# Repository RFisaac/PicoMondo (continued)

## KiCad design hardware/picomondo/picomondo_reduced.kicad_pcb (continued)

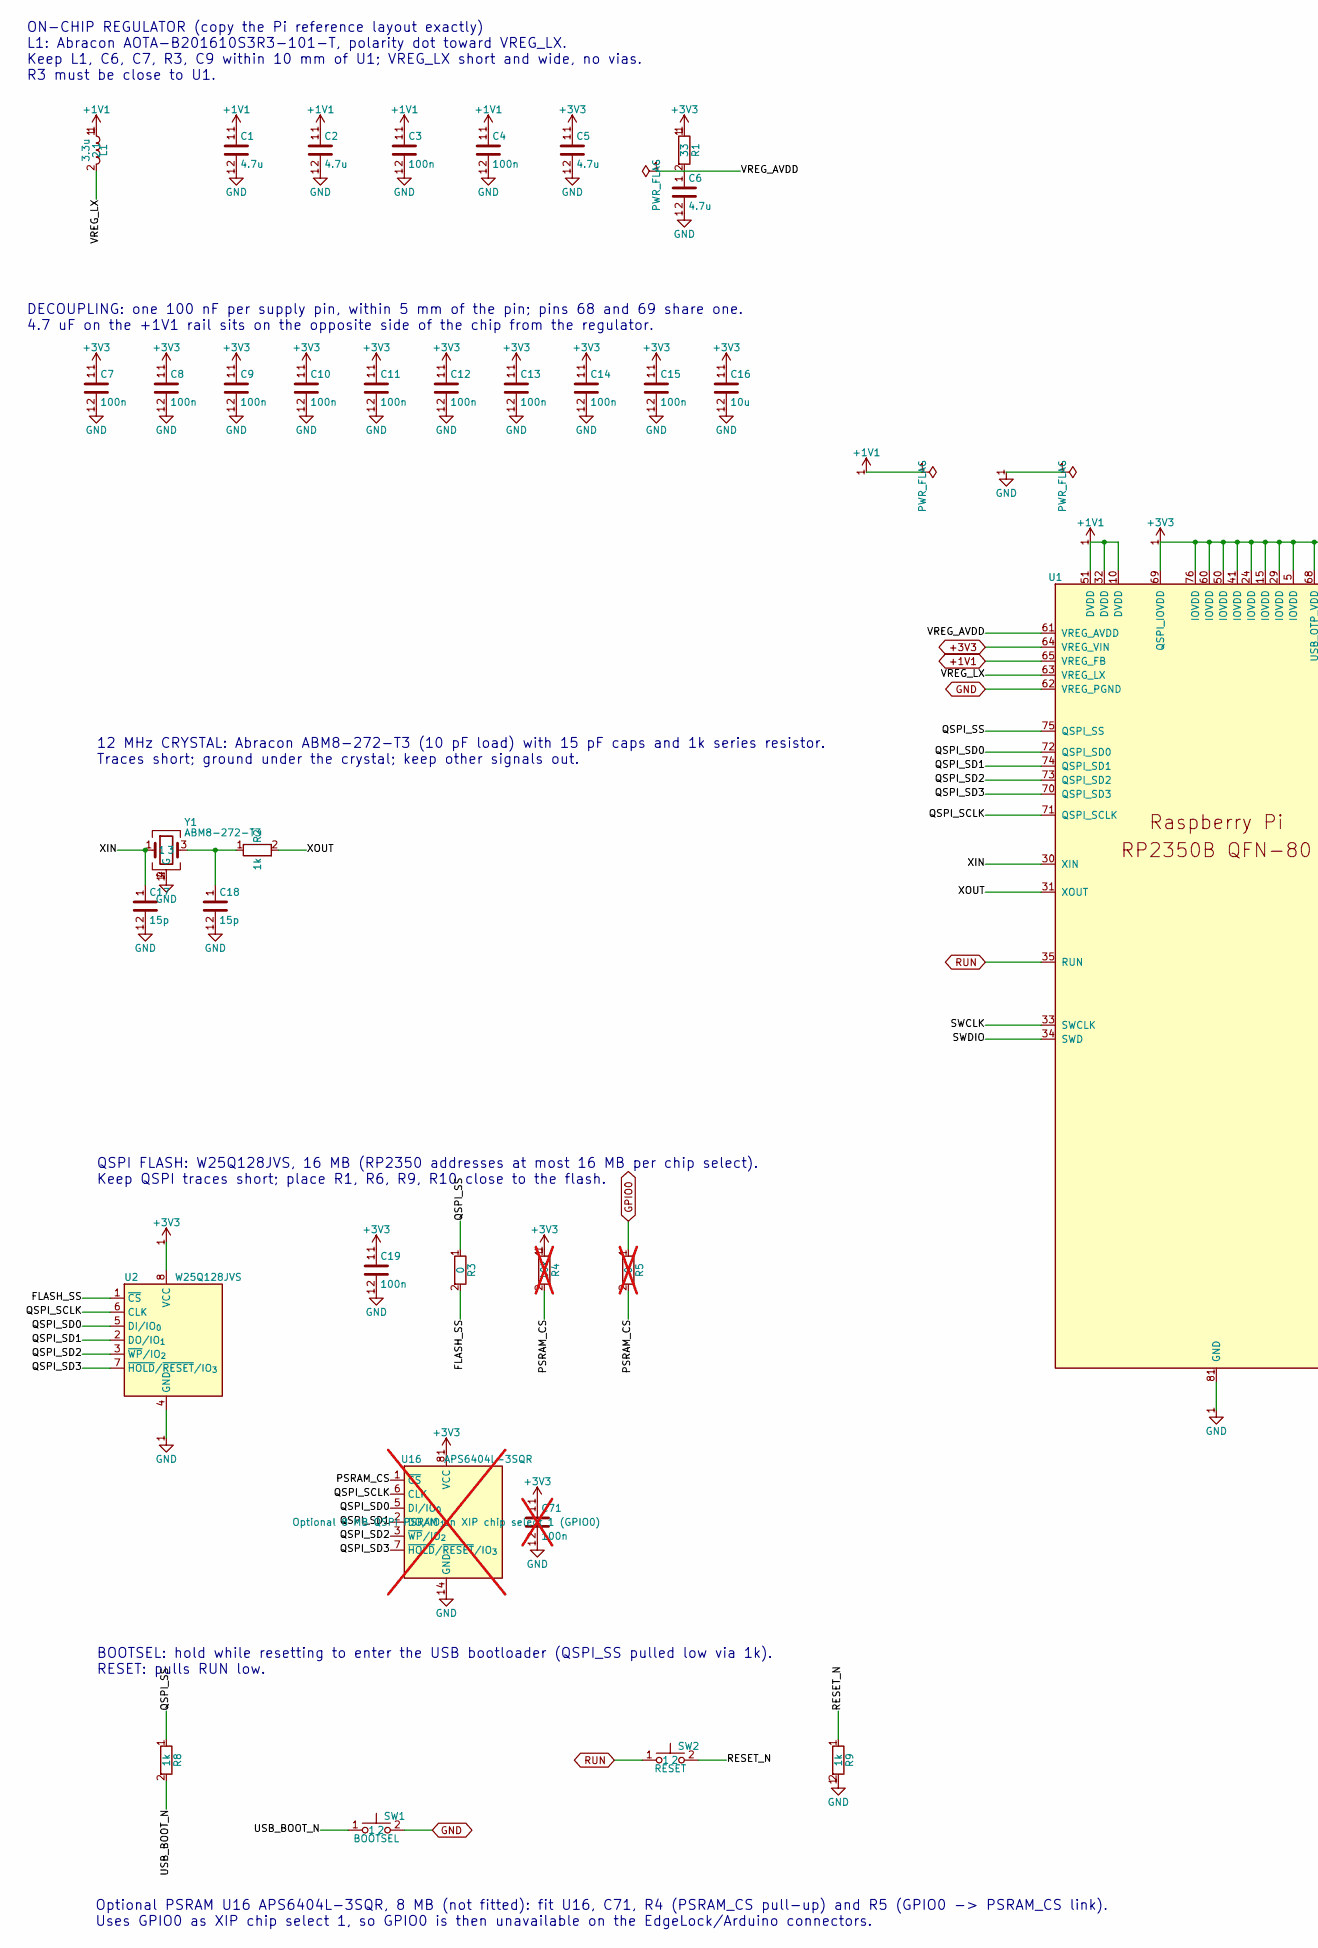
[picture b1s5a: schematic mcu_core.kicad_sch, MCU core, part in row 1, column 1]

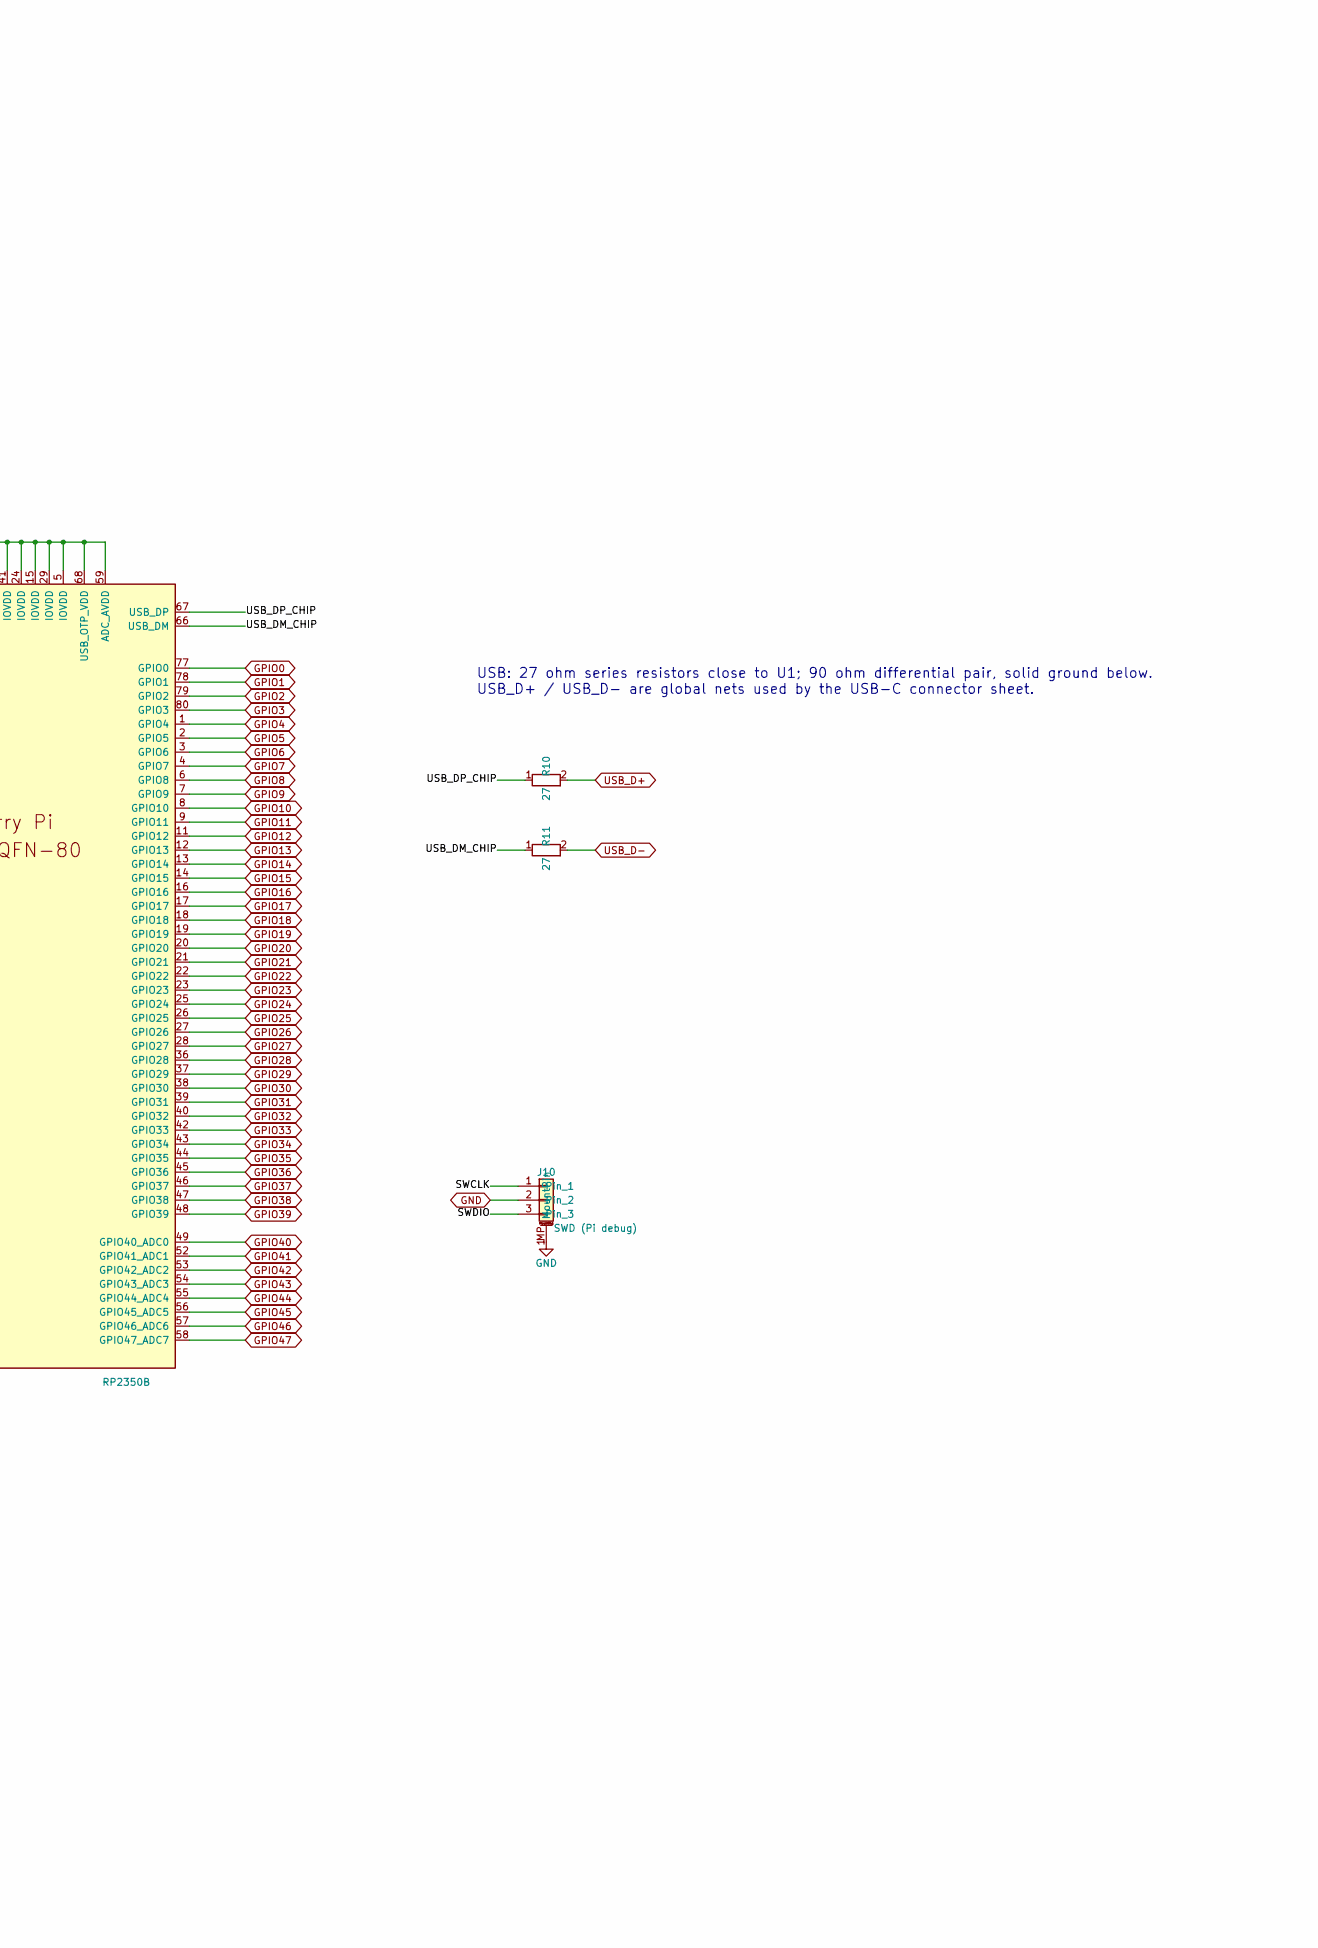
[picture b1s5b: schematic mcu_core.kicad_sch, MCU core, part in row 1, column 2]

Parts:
C1, C2, C5, C6: 4.7u; C_0402_1005Metric_small_pads; MPN CL05A475MP5NRNC; LCSC C23733
C3, C4, C7, C8, C9, C10, C11, C12, C13, C14, C15, C19: 100n; C_0402_1005Metric; MPN CL05B104KB54PNC; LCSC C307331
C16: 10u; C_0805_2012Metric; MPN CL21A106KAYNNNE; LCSC C15850
C17, C18: 15p; C_0402_1005Metric; MPN CC0402JRNPO9BN150; LCSC C106997
C71: 100n; C_0402_1005Metric; MPN CL05B104KB54PNC; LCSC C307331; not fitted
J10: SWD (Pi debug); JST_SH_SM03B-SRSS-TB_1x03-1MP_P1.00mm_Horizontal; MPN SM03B-SRSS-TB(LF)(SN); LCSC C160403
L1: 3.3u; L_pol_2016; MPN AOTA-B201610S3R3-101-T; LCSC C42411119
R1: 33; R_0402_1005Metric; MPN 0402WGF330JTCE; LCSC C25105
R2, R8, R9: 1k; R_0402_1005Metric; MPN 0402WGF1001TCE; LCSC C11702
R3: 0; R_0402_1005Metric; MPN 0402WGF0000TCE; LCSC C17168
R4: 10k; R_0402_1005Metric; MPN 0402WGF1002TCE; LCSC C25744; not fitted
R5: 0; R_0402_1005Metric; MPN 0402WGF0000TCE; LCSC C17168; not fitted
R10, R11: 27; R_0402_1005Metric; MPN 0402WGF270JTCE; LCSC C25100
SW1: BOOTSEL; SW_SMD_TS-1187A_5.1x5.1; MPN TS-1187A-B-A-B; LCSC C318884
SW2: RESET; SW_SMD_TS-1187A_5.1x5.1; MPN TS-1187A-B-A-B; LCSC C318884
U1: RP2350B; RP2350-QFN-80-1EP_10x10_P0.4mm_EP3.4x3.4mm_ThermalVias; MPN RP2350B; LCSC C42415655
U2: W25Q128JVS; SOIC-8_5.3x5.3mm_P1.27mm; MPN W25Q128JVSIQ; LCSC C97521
U16: APS6404L-3SQR; SOIC-8_3.9x4.9mm_P1.27mm; MPN APS6404L-3SQR-SN; LCSC C5333729; not fitted
Y1: ABM8-272-T3; Crystal_SMD_3225-4Pin_3.2x2.5mm; MPN ABM8-272-T3; LCSC C20625731

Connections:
+1V1: C1.1, C2.1, C3.1, C4.1, L1.1, U1.10 (DVDD), U1.32 (DVDD), U1.51 (DVDD), U1.65 (VREG_FB); also elsewhere on the board
+3V3: C5.1, C7.1, C8.1, C9.1, C10.1, C11.1, C12.1, C13.1, C14.1, C15.1, C16.1, C19.1, C71.1, R1.1, R4.1, U1.5 (IOVDD), U1.15 (IOVDD), U1.24 (IOVDD), U1.29 (IOVDD), U1.41 (IOVDD), U1.50 (IOVDD), U1.59 (ADC_AVDD), U1.60 (IOVDD), U1.64 (VREG_VIN), U1.68 (USB_OTP_VDD), U1.69 (QSPI_IOVDD), U1.76 (IOVDD), U2.8 (VCC), U16.8 (VCC); also elsewhere on the board
/MCU core/FLASH_SS: R3.2, U2.1 (~CS)
/MCU core/PSRAM_CS: R4.2, R5.2, U16.1 (~CS)
/MCU core/QSPI_SCLK: U1.71 (QSPI_SCLK), U2.6 (CLK), U16.6 (CLK)
/MCU core/QSPI_SD0: U1.72 (QSPI_SD0), U2.5 (DI/IO_{0}), U16.5 (DI/IO_{0})
/MCU core/QSPI_SD1: U1.74 (QSPI_SD1), U2.2 (DO/IO_{1}), U16.2 (DO/IO_{1})
/MCU core/QSPI_SD2: U1.73 (QSPI_SD2), U2.3 (~WP/IO_{2}), U16.3 (~WP/IO_{2})
/MCU core/QSPI_SD3: U1.70 (QSPI_SD3), U2.7 (~HOLD/~RESET/IO_{3}), U16.7 (~HOLD/~RESET/IO_{3})
/MCU core/QSPI_SS: R3.1, R8.1, U1.75 (QSPI_SS)
/MCU core/RESET_N: R9.1, SW2.2
/MCU core/SWCLK: J10.1, U1.33 (SWCLK)
/MCU core/SWDIO: J10.3, U1.34 (SWD)
/MCU core/USB_BOOT_N: R8.2, SW1.1
/MCU core/USB_DM_CHIP: R11.1, U1.66 (USB_DM)
/MCU core/USB_DP_CHIP: R10.1, U1.67 (USB_DP)
/MCU core/VREG_AVDD: C6.1, R1.2, U1.61 (VREG_AVDD)
/MCU core/VREG_LX: L1.2, U1.63 (VREG_LX)
/MCU core/XIN: C17.1, U1.30 (XIN), Y1.1
/MCU core/XOUT: R2.2, U1.31 (XOUT)
GND: C1.2, C2.2, C3.2, C4.2, C5.2, C6.2, C7.2, C8.2, C9.2, C10.2, C11.2, C12.2, C13.2, C14.2, C15.2, C16.2, C17.2, C18.2, C19.2, C71.2, J10.2, J10.MP (MountPin), R9.2, SW1.2, U1.62 (VREG_PGND), U1.81 (GND), U2.4 (GND), U16.4 (GND), Y1.2 (G), Y1.4 (G); also elsewhere on the board
GPIO0: R5.1, U1.77 (GPIO0); also elsewhere on the board
GPIO1: U1.78 (GPIO1); also elsewhere on the board
GPIO2: U1.79 (GPIO2); also elsewhere on the board
GPIO3: U1.80 (GPIO3); also elsewhere on the board
GPIO4: U1.1 (GPIO4); also elsewhere on the board
GPIO5: U1.2 (GPIO5); also elsewhere on the board
GPIO6: U1.3 (GPIO6); also elsewhere on the board
GPIO7: U1.4 (GPIO7); also elsewhere on the board
GPIO8: U1.6 (GPIO8); also elsewhere on the board
GPIO9: U1.7 (GPIO9); also elsewhere on the board
GPIO10: U1.8 (GPIO10); also elsewhere on the board
GPIO11: U1.9 (GPIO11); also elsewhere on the board
GPIO12: U1.11 (GPIO12); also elsewhere on the board
GPIO13: U1.12 (GPIO13); also elsewhere on the board
GPIO14: U1.13 (GPIO14); also elsewhere on the board
GPIO15: U1.14 (GPIO15); also elsewhere on the board
GPIO16: U1.16 (GPIO16); also elsewhere on the board
GPIO17: U1.17 (GPIO17); also elsewhere on the board
GPIO18: U1.18 (GPIO18); also elsewhere on the board
GPIO19: U1.19 (GPIO19); also elsewhere on the board
GPIO20: U1.20 (GPIO20); also elsewhere on the board
GPIO21: U1.21 (GPIO21); also elsewhere on the board
GPIO22: U1.22 (GPIO22); also elsewhere on the board
GPIO23: U1.23 (GPIO23); also elsewhere on the board
GPIO24: U1.25 (GPIO24); also elsewhere on the board
GPIO25: U1.26 (GPIO25); also elsewhere on the board
GPIO26: U1.27 (GPIO26); also elsewhere on the board
GPIO27: U1.28 (GPIO27); also elsewhere on the board
GPIO28: U1.36 (GPIO28); also elsewhere on the board
GPIO29: U1.37 (GPIO29); also elsewhere on the board
GPIO30: U1.38 (GPIO30); also elsewhere on the board
GPIO31: U1.39 (GPIO31); also elsewhere on the board
GPIO32: U1.40 (GPIO32); also elsewhere on the board
GPIO33: U1.42 (GPIO33); also elsewhere on the board
GPIO34: U1.43 (GPIO34); also elsewhere on the board
GPIO35: U1.44 (GPIO35); also elsewhere on the board
GPIO36: U1.45 (GPIO36); also elsewhere on the board
GPIO37: U1.46 (GPIO37); also elsewhere on the board
GPIO38: U1.47 (GPIO38); also elsewhere on the board
GPIO39: U1.48 (GPIO39); also elsewhere on the board
GPIO40: U1.49 (GPIO40_ADC0); also elsewhere on the board
GPIO41: U1.52 (GPIO41_ADC1); also elsewhere on the board
GPIO42: U1.53 (GPIO42_ADC2); also elsewhere on the board
GPIO43: U1.54 (GPIO43_ADC3); also elsewhere on the board
GPIO44: U1.55 (GPIO44_ADC4); also elsewhere on the board
GPIO45: U1.56 (GPIO45_ADC5); also elsewhere on the board
GPIO46: U1.57 (GPIO46_ADC6); also elsewhere on the board
GPIO47: U1.58 (GPIO47_ADC7); also elsewhere on the board
unnamed: C18.1, R2.1, Y1.3
RUN: SW2.1, U1.35 (RUN)
USB_D+: R10.2; also elsewhere on the board
USB_D-: R11.2; also elsewhere on the board

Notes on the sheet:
BOOTSEL: hold while resetting to enter the USB bootloader (QSPI_SS pulled low via 1k). RESET: pulls RUN low.
12 MHz CRYSTAL: Abracon ABM8-272-T3 (10 pF load) with 15 pF caps and 1k series resistor. Traces short; ground under the crystal; keep other signals out.
ON-CHIP REGULATOR (copy the Pi reference layout exactly) L1: Abracon AOTA-B201610S3R3-101-T, polarity dot toward VREG_LX. Keep L1, C6, C7, R3, C9 within 10 mm of U1; VREG_LX short and wide, no vias. R3 must be close to U1.
Optional PSRAM U16 APS6404L-3SQR, 8 MB (not fitted): fit U16, C71, R4 (PSRAM_CS pull-up) and R5 (GPIO0 -> PSRAM_CS link). Uses GPIO0 as XIP chip select 1, so GPIO0 is then unavailable on the EdgeLock/Arduino connectors.
QSPI FLASH: W25Q128JVS, 16 MB (RP2350 addresses at most 16 MB per chip select). Keep QSPI traces short; place R1, R6, R9, R10 close to the flash.
DECOUPLING: one 100 nF per supply pin, within 5 mm of the pin; pins 68 and 69 share one. 4.7 uF on the +1V1 rail sits on the opposite side of the chip from the regulator.
USB: 27 ohm series resistors close to U1; 90 ohm differential pair, solid ground below. USB_D+ / USB_D- are global nets used by the USB-C connector sheet.

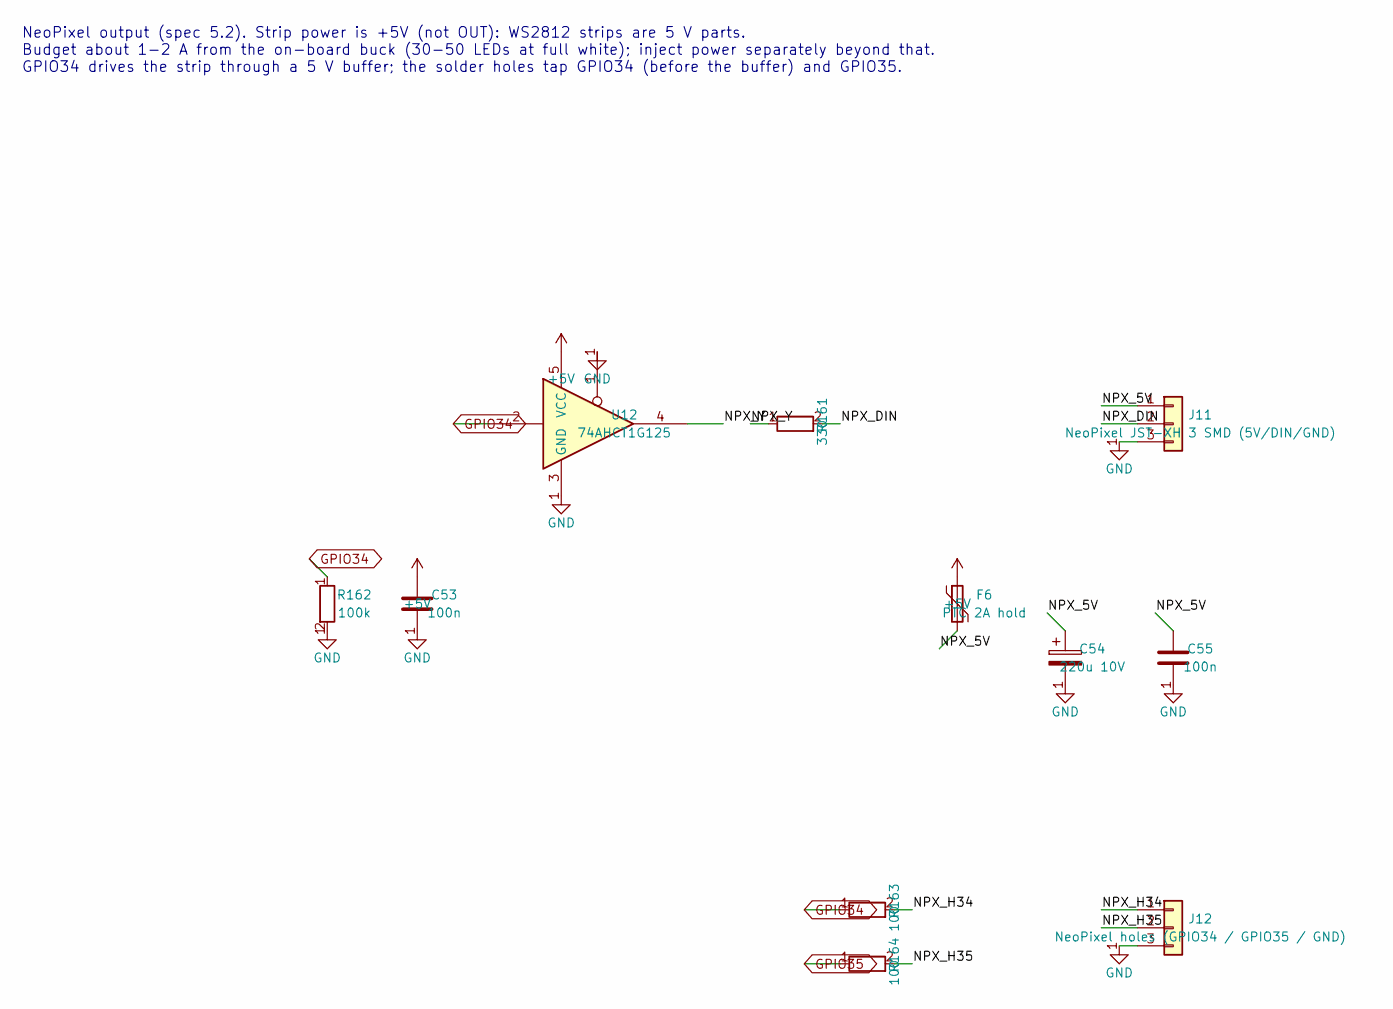
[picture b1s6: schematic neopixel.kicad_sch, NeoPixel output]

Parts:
C53, C55: 100n; C_0402_1005Metric; MPN CL05B104KB54PNC; LCSC C307331
C54: 220u 10V; CP_Elec_6.3x7.7; MPN VMMC0771A221MV; LCSC C487024
F6: PTC 2A hold; F1812; MPN SMD1812P200TF/16; LCSC C20812
J11: NeoPixel JST-XH 3 SMD (5V/DIN/GND); JST_XH_S3B-XH-SM4-TB_1x03-1MP_P2.50mm_Horizontal; MPN S3B-XH-SM4-TB(LF)(SN)
J12: NeoPixel holes (GPIO34 / GPIO35 / GND); PinHeader_1x03_P2.54mm_Vertical
R161: 330; R_0402_1005Metric; MPN 0402WGF3300TCE; LCSC C25104
R162: 100k; R_0402_1005Metric; MPN 0402WGF1003TCE; LCSC C25741
R163, R164: 100; R_0402_1005Metric; MPN 0402WGF1000TCE; LCSC C25076
U12: 74AHCT1G125; SOT-353_SC-70-5; MPN 74AHCT1G125GW,125; LCSC C12495

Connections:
+5V: C53.1, F6.1, U12.5 (VCC); also elsewhere on the board
/NeoPixel and Qwiic/NPX_5V: C54.1, C55.1, F6.2, J11.1
/NeoPixel and Qwiic/NPX_DIN: J11.2, R161.2
/NeoPixel and Qwiic/NPX_H34: J12.1, R163.2
/NeoPixel and Qwiic/NPX_H35: J12.2, R164.2
/NeoPixel and Qwiic/NPX_Y: R161.1, U12.4
GND: C53.2, C54.2, C55.2, J11.3, J12.3, R162.2, U12.1, U12.3 (GND); also elsewhere on the board
GPIO34: R162.1, R163.1, U12.2; also elsewhere on the board
GPIO35: R164.1; also elsewhere on the board

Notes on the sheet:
NeoPixel output (spec 5.2). Strip power is +5V (not OUT): WS2812 strips are 5 V parts. Budget about 1-2 A from the on-board buck (30-50 LEDs at full white); inject power separately beyond that. GPIO34 drives the strip through a 5 V buffer; the solder holes tap GPIO34 (before the buffer) and GPIO35.

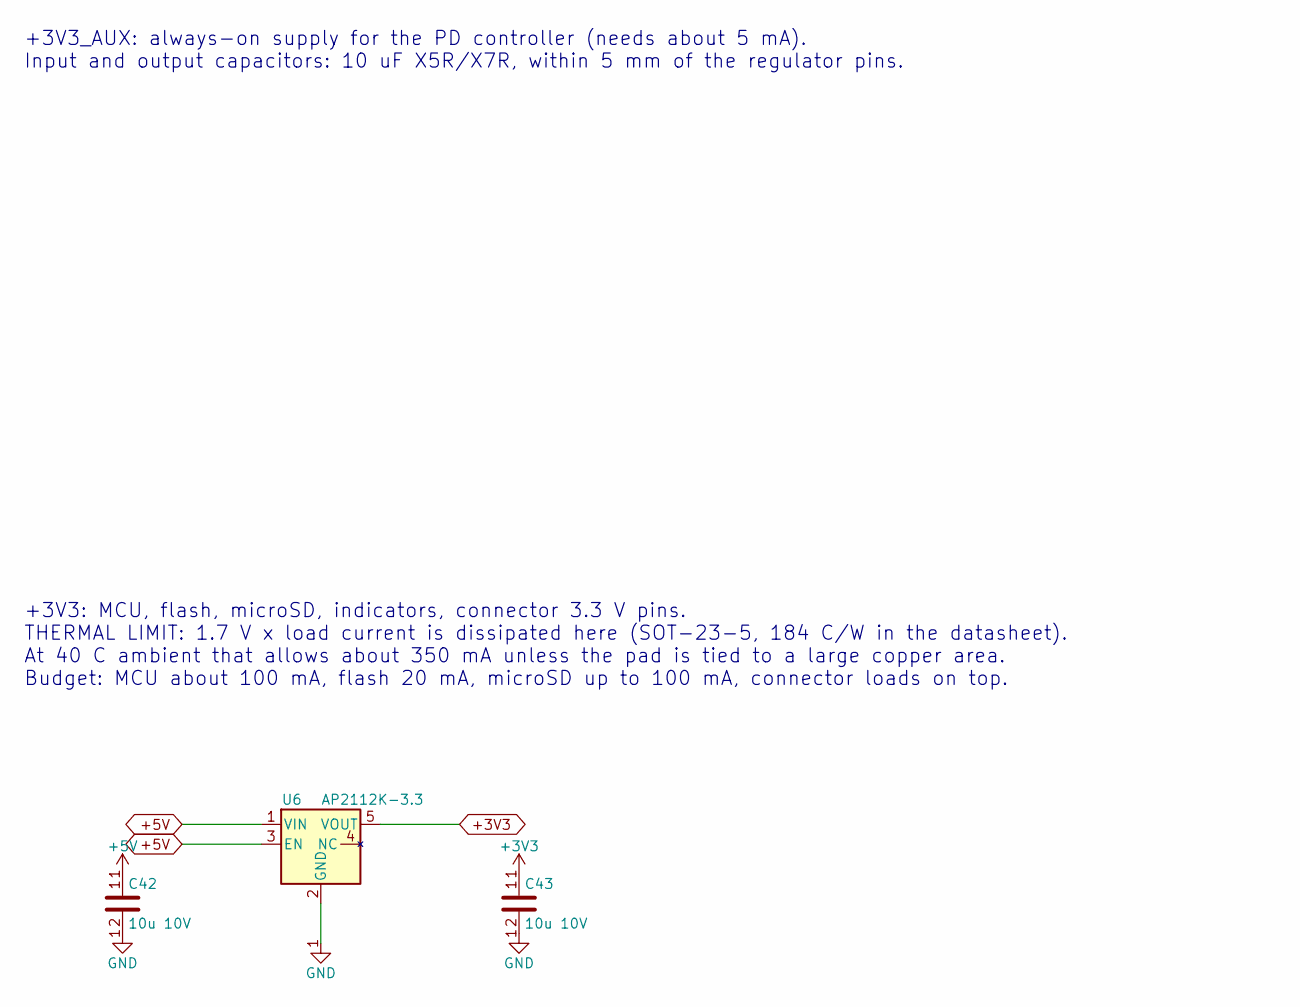
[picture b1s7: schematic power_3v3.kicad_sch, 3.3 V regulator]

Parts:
C42, C43: 10u 10V; C_0805_2012Metric; MPN CL21A106KAYNNNE; LCSC C15850
U6: AP2112K-3.3; SOT-23-5; MPN AP2112K-3.3TRG1; LCSC C51118

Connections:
+3V3: C43.1, U6.5 (VOUT); also elsewhere on the board
+5V: C42.1, U6.1 (VIN), U6.3 (EN); also elsewhere on the board
GND: C42.2, C43.2, U6.2 (GND); also elsewhere on the board

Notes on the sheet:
+3V3_AUX: always-on supply for the PD controller (needs about 5 mA). Input and output capacitors: 10 uF X5R/X7R, within 5 mm of the regulator pins.
+3V3: MCU, flash, microSD, indicators, connector 3.3 V pins. THERMAL LIMIT: 1.7 V x load current is dissipated here (SOT-23-5, 184 C/W in the datasheet). At 40 C ambient that allows about 350 mA unless the pad is tied to a large copper area. Budget: MCU about 100 mA, flash 20 mA, microSD up to 100 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

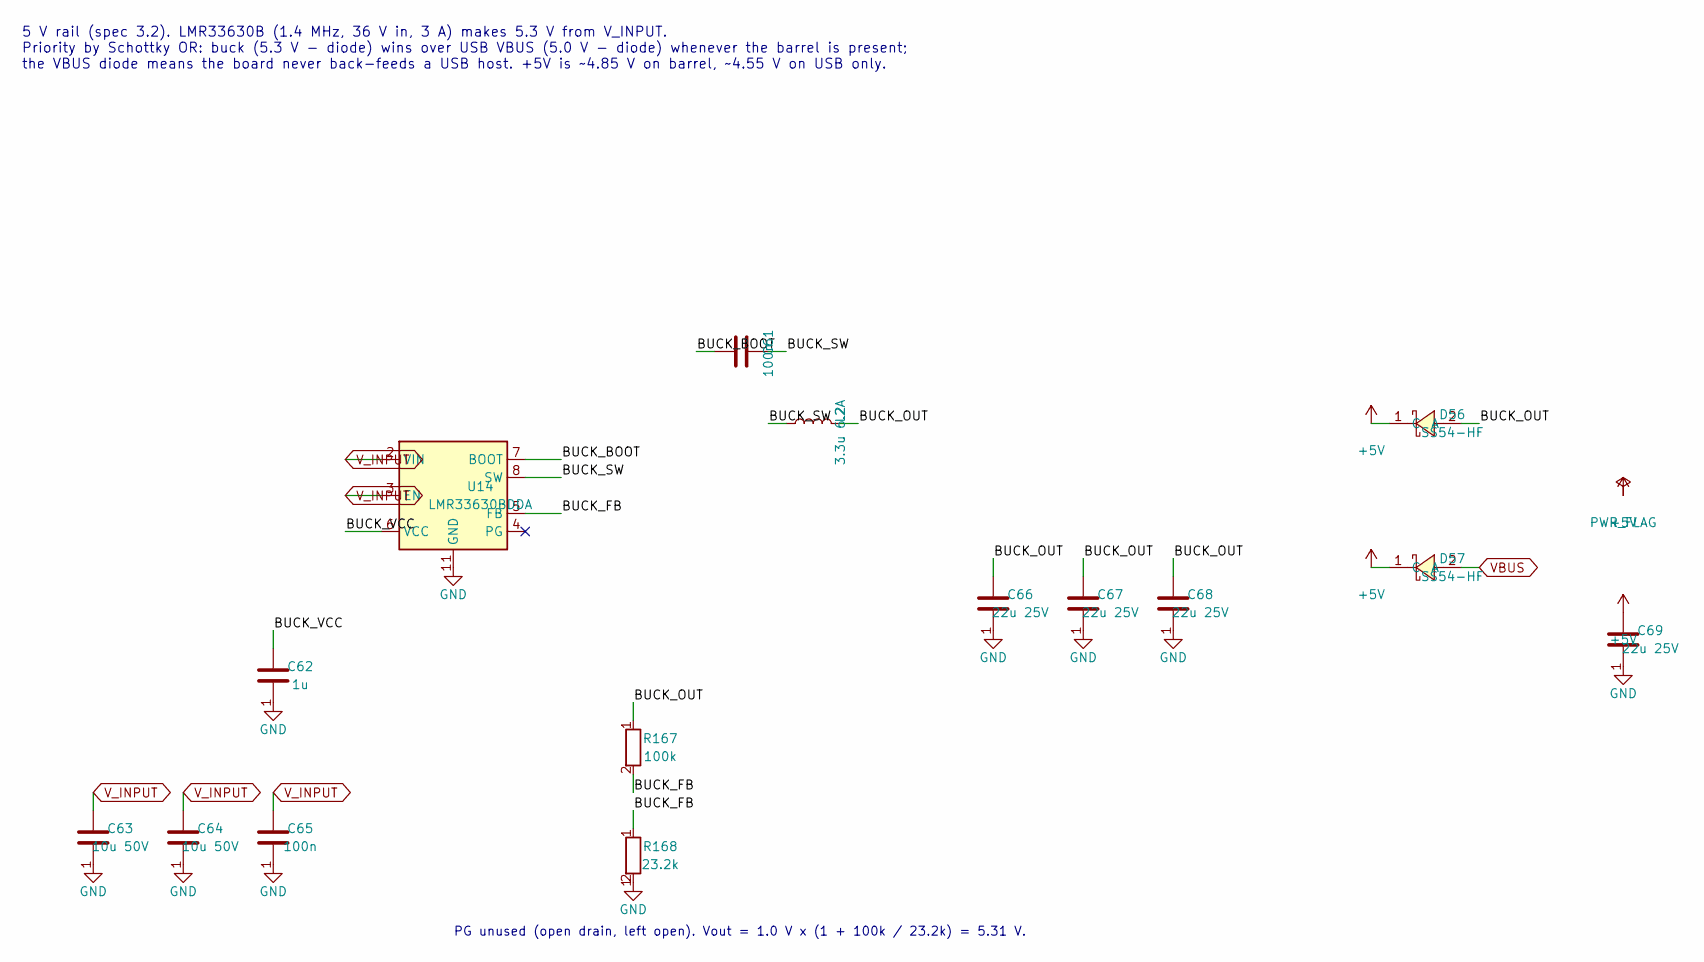
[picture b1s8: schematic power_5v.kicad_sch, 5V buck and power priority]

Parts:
C61, C65: 100n; C_0402_1005Metric; MPN CL05B104KB54PNC; LCSC C307331
C62: 1u; C_0402_1005Metric; MPN CL05A105KA5NQNC; LCSC C52923
C63, C64: 10u 50V; C_1206_3216Metric; MPN CL31A106KBHNNNE; LCSC C13585
C66, C67, C68, C69: 22u 25V; C_1206_3216Metric; MPN CL31A226KAHNNNE; LCSC C12891
D56, D57: SS54-HF; SMA_L4.3-W2.5-LS5.0-RD; MPN SS54-HF; LCSC C3757794
L2: 3.3u 6.2A; L_Sunlord_SWPA6045S; MPN SWPA6045S3R3NT; LCSC C279943
R167: 100k; R_0402_1005Metric; MPN 0402WGF1003TCE; LCSC C25741
R168: 23.2k; R_0402_1005Metric; MPN RC0402FR-0723K2L
U14: LMR33630BDDA; Texas_HSOP-8-1EP_3.9x4.9mm_P1.27mm_ThermalVias; MPN LMR33630BDDAR; LCSC C544370

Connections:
+5V: C69.1, D56.1 (C), D57.1 (C); also elsewhere on the board
/5V and power priority/BUCK_BOOT: C61.1, U14.7 (BOOT)
/5V and power priority/BUCK_FB: R167.2, R168.1, U14.5 (FB)
/5V and power priority/BUCK_OUT: C66.1, C67.1, C68.1, D56.2 (A), L2.2, R167.1
/5V and power priority/BUCK_SW: C61.2, L2.1, U14.8 (SW)
/5V and power priority/BUCK_VCC: C62.1, U14.6 (VCC)
GND: C62.2, C63.2, C64.2, C65.2, C66.2, C67.2, C68.2, C69.2, R168.2, U14.1 (GND), U14.9 (GND); also elsewhere on the board
VBUS: D57.2 (A); also elsewhere on the board
V_INPUT: C63.1, C64.1, C65.1, U14.2 (VIN), U14.3 (EN); also elsewhere on the board

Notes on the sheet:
PG unused (open drain, left open). Vout = 1.0 V x (1 + 100k / 23.2k) = 5.31 V.
5 V rail (spec 3.2). LMR33630B (1.4 MHz, 36 V in, 3 A) makes 5.3 V from V_INPUT. Priority by Schottky OR: buck (5.3 V - diode) wins over USB VBUS (5.0 V - diode) whenever the barrel is present; the VBUS diode means the board never back-feeds a USB host. +5V is ~4.85 V on barrel, ~4.55 V on USB only.

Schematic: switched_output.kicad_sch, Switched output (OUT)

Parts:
C45: 100n; C_0402_1005Metric; MPN CL05B104KB54PNC; LCSC C307331
D6: BZT52C12 12V; D_SOD-123; MPN BZT52C12-13-F; LCSC C177013
D7: SS54-HF; SMA_L4.3-W2.5-LS5.0-RD; MPN SS54-HF; LCSC C3757794
D8: red; LED_0603_1608Metric; MPN KT-0603R; LCSC C2286
F3: 3A hold 33V; F1812; MPN 1812L300/33GR; LCSC C54300298
J8: OUT EdgeLock 4 (2+2); EdgeLock_4ckt_Molex2008900104; MPN 2008900104
J9: OUT heavy holes; EdgeLock_4ckt_HeavyHoles
Q5: DMP4015SSS-13; SO-8_L4.9-W3.9-P1.27-LS5.9-BL; MPN DMP4015SSS-13; LCSC C508210
Q6: MMBT3904; SOT-23; MPN MMBT3904LT1G; LCSC C81464
R27: 20m 1% 2W; R2512; MPN GX2512-2W-20mR-1%; LCSC C500720
R28: 47k; R_0402_1005Metric; MPN 0402WGF4702TCE; LCSC C25792
R29: 22k; R_0603_1608Metric; MPN 0603WAF2202T5E; LCSC C31850
R30, R37: 10k; R_0402_1005Metric; MPN 0402WGF1002TCE; LCSC C25744
R31: 100k; R_0402_1005Metric; MPN 0402WGF1003TCE; LCSC C25741
R32: 22k; R_0402_1005Metric; MPN 0402WGF2202TCE; LCSC C25768
U8: INA226 (0x41); MSOP-10_3x3mm_P0.5mm; MPN INA226AIDGSR; LCSC C49851

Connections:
+3V3: C45.1, U8.2 (A0), U8.6 (VS); also elsewhere on the board
/Switched outputs/J8_BASE: Q6.1 (B), R30.2, R31.1
/Switched outputs/J8_DRAIN: F3.1, Q5.5 (D), Q5.6 (D), Q5.7 (D), Q5.8 (D)
/Switched outputs/J8_GATE: D6.2 (A), Q5.4 (G), R28.2, R29.1
/Switched outputs/J8_GCOL: Q6.3 (C), R29.2
/Switched outputs/J8_OUT: D7.1 (C), F3.2, J8.1, J8.2, J9.1, R32.1, R37.1
/Switched outputs/J8_SRC: D6.1 (K), Q5.1 (S), Q5.2 (S), Q5.3 (S), R27.2, R28.1, U8.8 (Vbus), U8.9 (Vin-)
/Switched outputs/SW_LED: D8.2 (A), R37.2
GND: C45.2, D7.2 (A), D8.1 (K), J8.3, J8.4, J9.2, Q6.2 (E), R31.2, R32.2, U8.1 (A1), U8.7 (GND); also elsewhere on the board
GPIO16: U8.4 (SDA); also elsewhere on the board
GPIO17: U8.5 (SCL); also elsewhere on the board
GPIO24: R30.1; also elsewhere on the board
V_INPUT: R27.1, U8.10 (Vin+); also elsewhere on the board

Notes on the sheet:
+5V_SW: switched 5 V for the J9 servo/motor connector, up to 3 A. GPIO24 high = on. No current monitor. The red LED shows the rail is on.
J7: switched 5 V output, up to 3 A. GPIO8 high = on. INA226 at I2C 0x40. Shunt 20 mohm: the INA226 input range is only +/-81.92 mV, so 3 A needs 27 mohm or less.
J8: switched V_INPUT output (about 5 V to 28 V), up to 3 A. GPIO9 high = on. INA226 at 0x41. 40 V P-FET with a 12 V zener limiting the gate-source voltage; INA226 is rated 36 V.

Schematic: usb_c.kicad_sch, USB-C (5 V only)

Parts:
C70: 4.7u; C_0805_2012Metric; MPN CL21A475KAQNNNE; LCSC C1779
J14: USB-C (USB4105-GF-A); TYPE-C-SMD_SBC-160S1A-20-S412; MPN USB4105-GF-A; LCSC C3020560
R170, R171: 5.1k; R_0402_1005Metric; MPN 0402WGF5101TCE; LCSC C25905
U15: USBLC6-2SC6; SOT-23-6_L2.9-W1.6-P0.95-LS2.8-BL; MPN USBLC6-2SC6; LCSC C7519

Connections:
/USB-C/CC1: J14.A5 (CC1), R170.1
/USB-C/CC2: J14.B5 (CC2), R171.1
GND: C70.2, J14.1 (EH), J14.2 (EH), J14.3 (EH), J14.4 (EH), J14.A1 (GND), J14.A12 (GND), J14.B1 (GND), J14.B12 (GND), R170.2, R171.2, U15.2; also elsewhere on the board
USB_D+: J14.A6 (DP1), J14.B6 (DP2), U15.1, U15.6; also elsewhere on the board
USB_D-: J14.A7 (DN1), J14.B7 (DN2), U15.3, U15.4; also elsewhere on the board
VBUS: C70.1, J14.A4 (VBUS), J14.A9 (VBUS), J14.B4 (VBUS), J14.B9 (VBUS), U15.5; also elsewhere on the board

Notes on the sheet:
USB-C, 5 V only (spec 2): 5.1k on CC1/CC2 (sink), USBLC6-2SC6 at the connector. D+/D- go straight to USB_D+/USB_D- (the 27R series resistors are on the MCU sheet). VBUS goes to the priority diode.

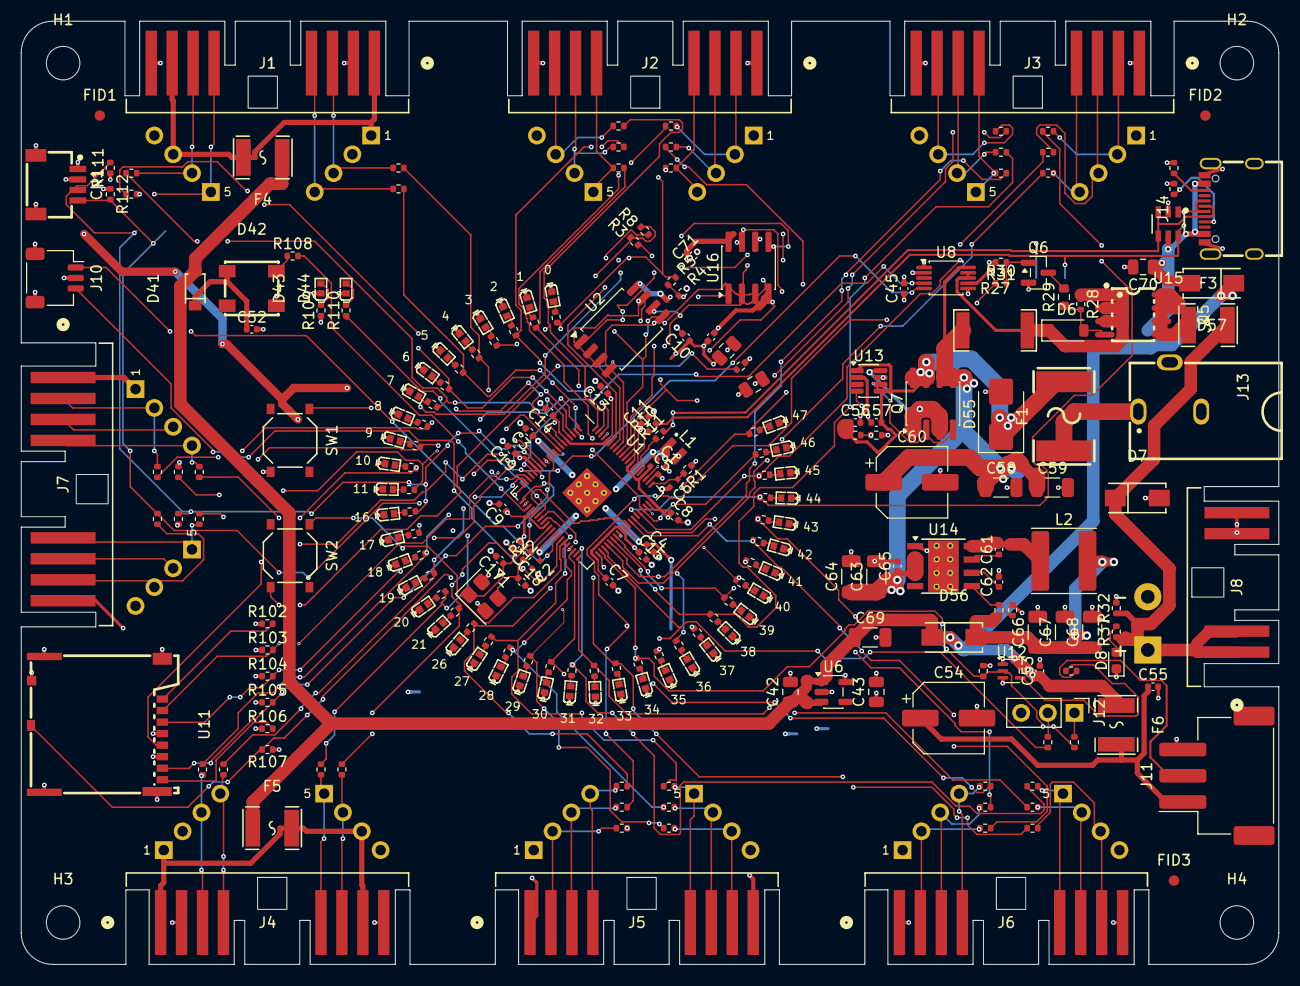
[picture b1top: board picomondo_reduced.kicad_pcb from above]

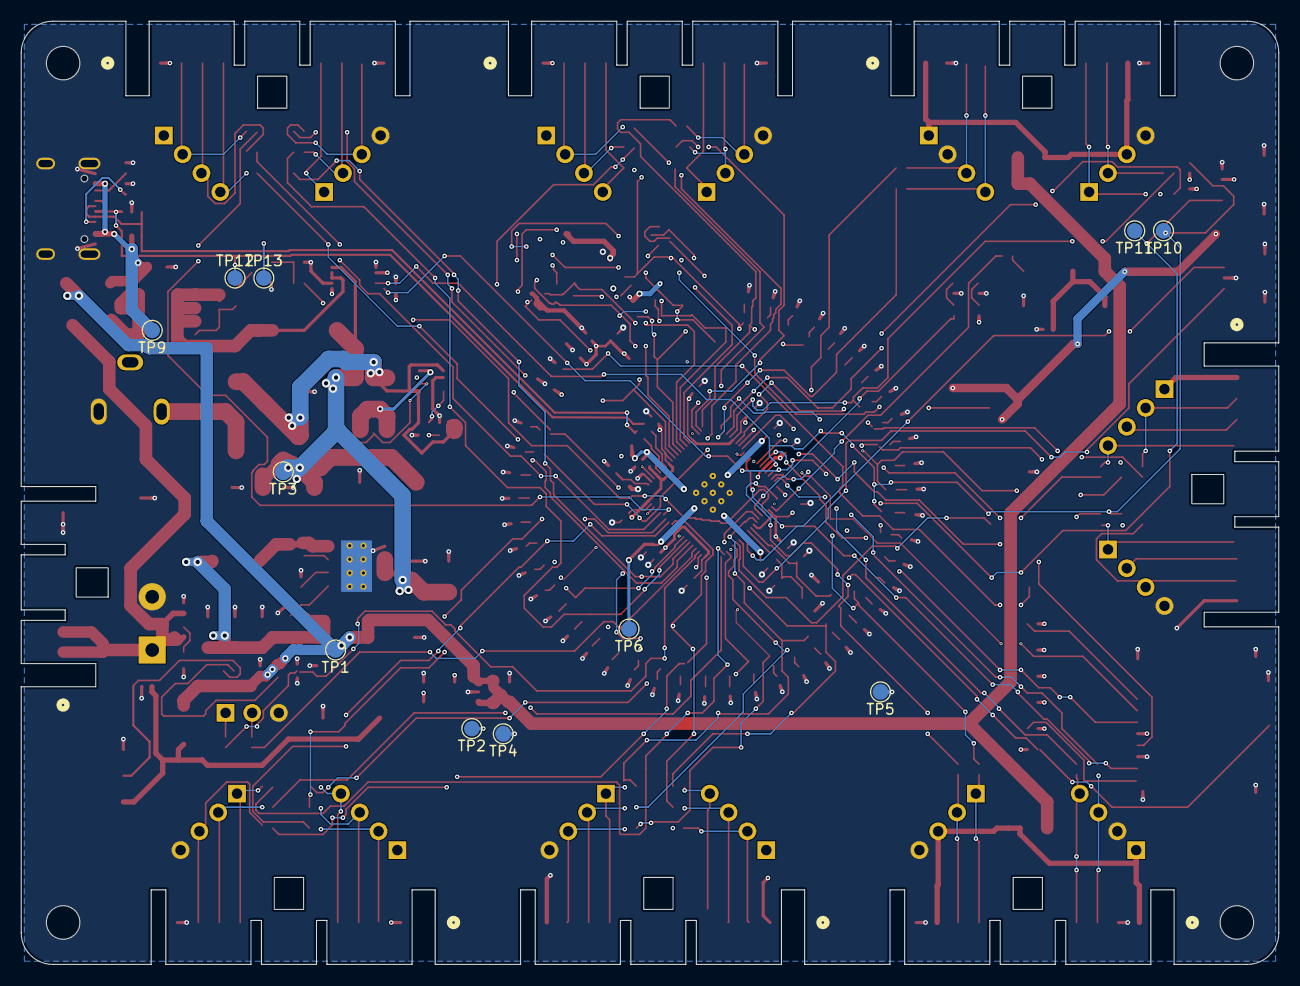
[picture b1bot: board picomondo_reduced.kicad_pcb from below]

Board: 4 copper layers, 120.0 x 90.0 mm, 272 parts (11 on the bottom side), 187 nets.
